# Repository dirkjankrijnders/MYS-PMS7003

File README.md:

# MYS-PMS7003
Mysensors experimental node with switch mode power supply, NRF24, arduino, ESP-03 and PM-7003

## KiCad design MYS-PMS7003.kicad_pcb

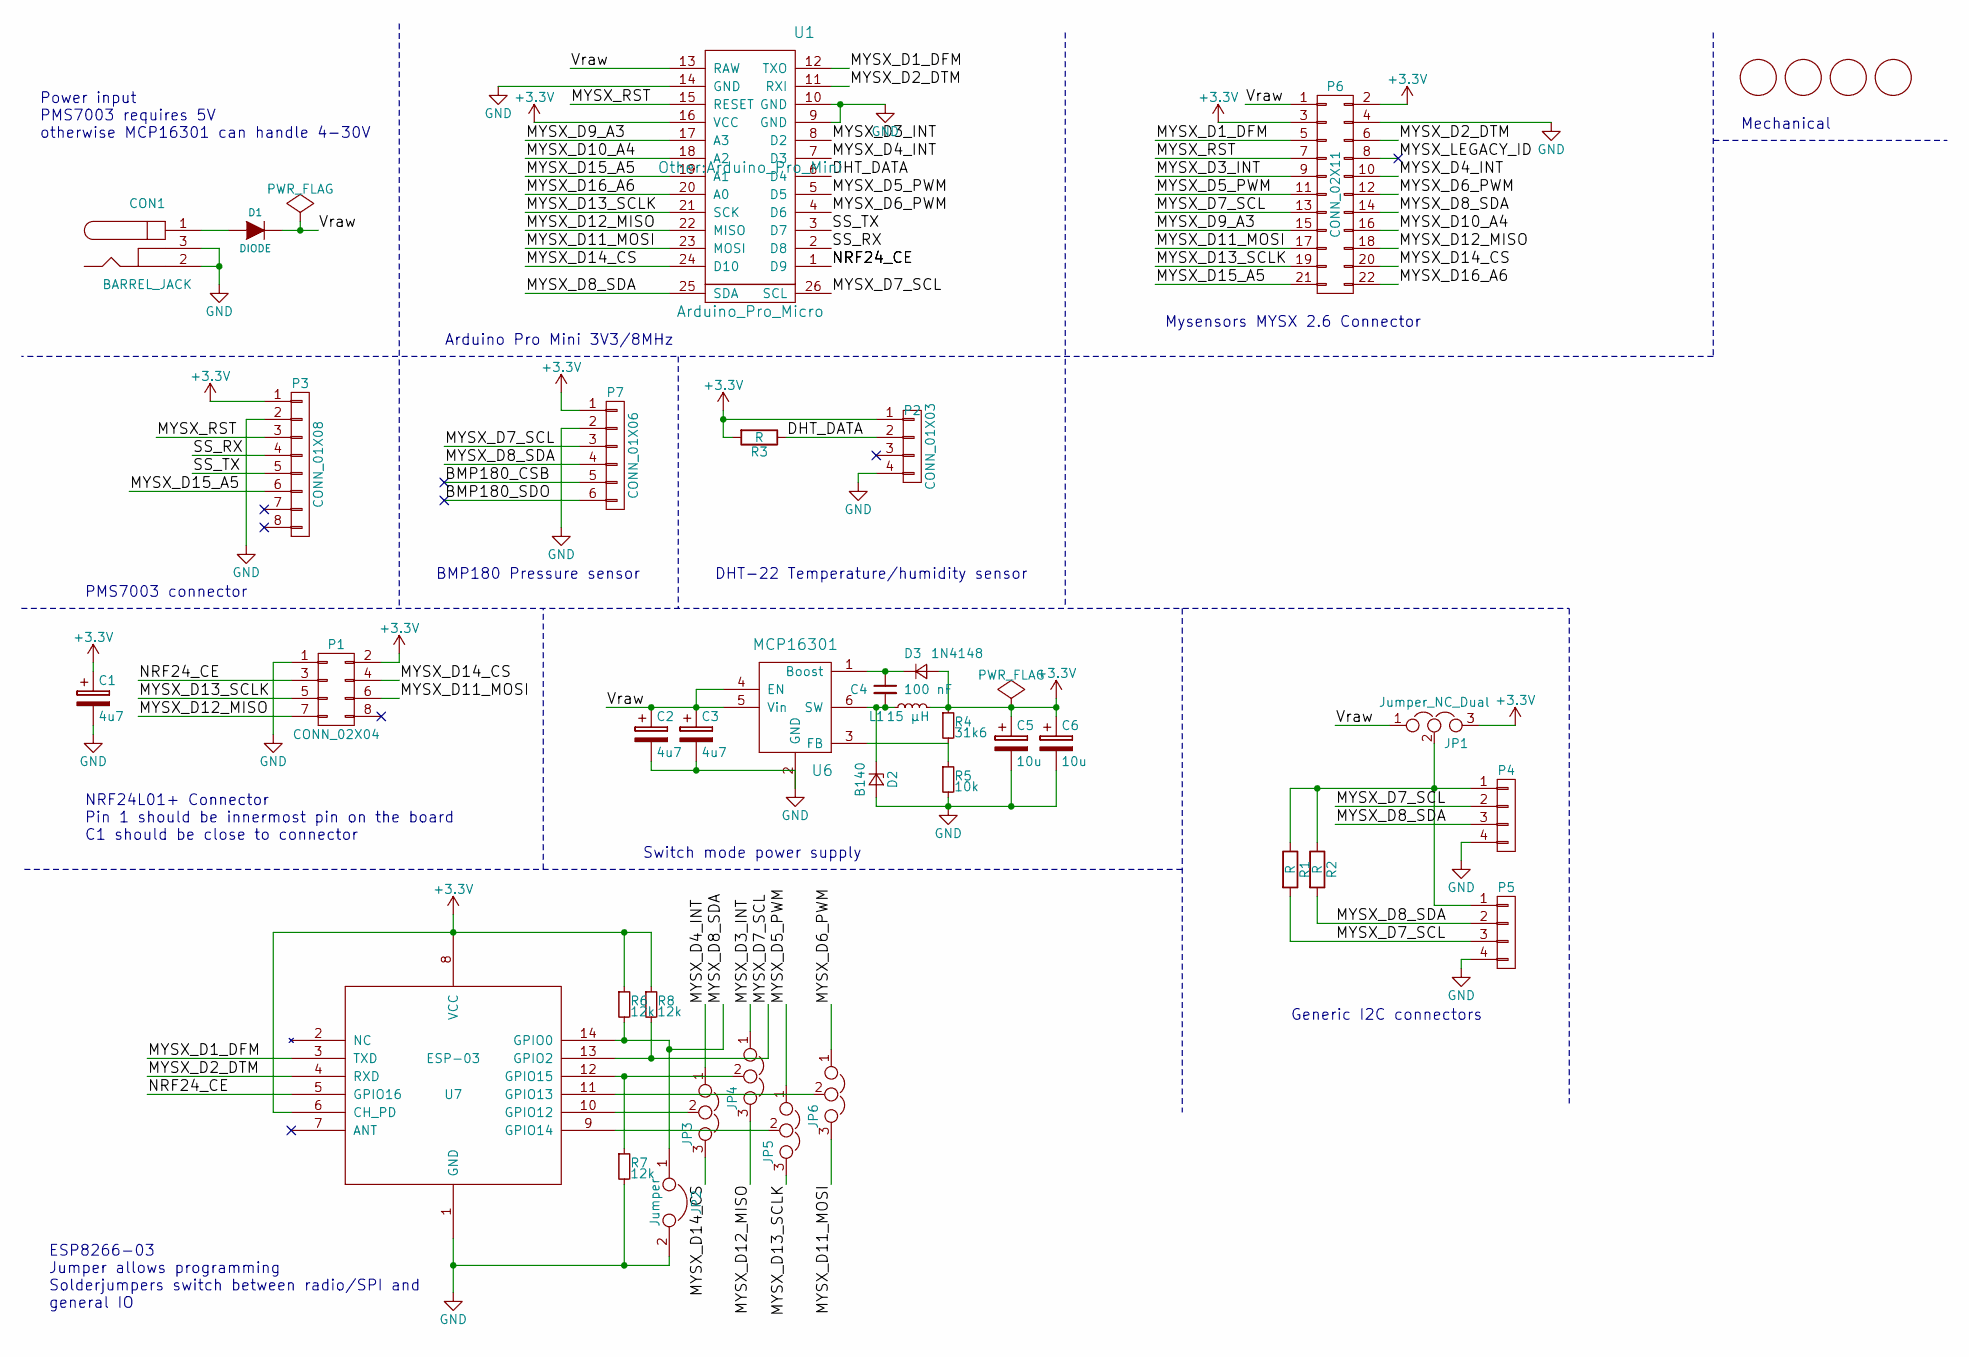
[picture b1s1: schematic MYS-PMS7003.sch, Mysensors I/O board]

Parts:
C1, C2, C3: 4u7; R_1210_HandSoldering
C4: 100 nF; R_0805_HandSoldering
C5, C6: 10u; R_0805_HandSoldering
CON1: BARREL_JACK
D1: DIODE; D_SMA-SMB_Universal_Handsoldering
D2: B140; D_SMA
D3: 1N4148; D_SOD-323_HandSoldering
JP1, JP3, JP4, JP5: Jumper_NC_Dual; Pin_Header_Straight_1x03_Pitch2.54mm
JP2: Jumper; Pin_Header_Angled_1x02_Pitch2.54mm
JP6: Jumper_NC_Dual; SolderJumper2way
L1: 15 μH; L_Coilcraft_MSS6132
P1: CONN_02X04; Pin_Header_Straight_2x04_Pitch2.54mm
P2: CONN_01X03; Pin_Header_Straight_1x04_Pitch2.54mm
P3: CONN_01X08; Pin_Header_Straight_1x08_Pitch1.27mm
P4, P5: CONN_01X04; Pin_Header_Straight_1x04_Pitch2.54mm
P6: CONN_02X11; Pin_Header_Straight_2x11_Pitch2.54mm
P7: CONN_01X06; Pin_Header_Straight_1x06_Pitch2.54mm
R1, R2, R3: R; R_0805_HandSoldering
R4: 31k6; R_0805_HandSoldering
R5: 10k; R_0805_HandSoldering
R6, R7, R8: 12k; R_0805_HandSoldering
U1: Arduino_Pro_Micro; Arduino_Pro_Mini
U2, U3, U4, U5: M3_Mounting_hole; MountingHole_3mm
U6: MCP16301; SOT-23-6_Handsoldering
U7: ESP-03

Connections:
+3V3: C1.1, C5.1, C6.1, D3.2 (A), JP1.3, L1.2, P1.2, P2.1, P3.1, P6.2, P6.3, P7.1, R3.2, R4.1, R6.1, R8.1, U1.16 (VCC), U7.6 (CH_PD), U7.8 (VCC); also elsewhere on the board
/BMP180_CSB: P7.5
/BMP180_SDO: P7.6
/DHT_DATA: P2.2, R3.1, U1.6 (D4)
/MYSX_D1_DFM: P6.5, U1.12 (TXO), U7.3 (TXD); also elsewhere on the board
/MYSX_D2_DTM: P6.6, U1.11 (RXI), U7.4 (RXD); also elsewhere on the board
/MYSX_D3_INT: JP4.1, P6.9, U1.8 (D2)
/MYSX_D4_INT: JP3.1, P6.10, U1.7 (D3)
/MYSX_D5_PWM: JP5.1, P6.11, U1.5 (D5)
/MYSX_D6_PWM: JP6.1, P6.12, U1.4 (D6)
/MYSX_D7_SCL: P4.2, P5.3, P6.13, P7.3, R1.2, R8.2, U1.26 (SCL), U7.13 (GPIO2); also elsewhere on the board
/MYSX_D8_SDA: JP2.1, P4.3, P5.2, P6.14, P7.4, R2.2, R6.2, U1.25 (SDA), U7.14 (GPIO0); also elsewhere on the board
/MYSX_D9_A3: P6.15, U1.17 (A3)
/MYSX_D10_A4: P6.16, U1.18 (A2)
/MYSX_D11_MOSI: JP6.3, P1.6, P6.17, U1.23 (MOSI)
/MYSX_D12_MISO: JP4.3, P1.7, P6.18, U1.22 (MISO)
/MYSX_D13_SCLK: JP5.3, P1.5, P6.19, U1.21 (SCK)
/MYSX_D14_CS: JP3.3, P1.4, P6.20, U1.24 (D10)
/MYSX_D15_A5: P3.6, P6.21, U1.19 (A1)
/MYSX_D16_A6: P6.22, U1.20 (A0)
/MYSX_LEGACY_ID: P6.8
/MYSX_RST: P3.3, P6.7, U1.15 (RESET)
/NRF24_CE: P1.3, U1.1 (D9), U7.5 (GPIO16); also elsewhere on the board
/SS_RX: P3.4, U1.2 (D8)
/SS_TX: P3.5, U1.3 (D7)
/Vraw: C2.1, C3.1, D1.2 (K), JP1.1, P6.1, U1.13 (RAW), U6.4 (EN), U6.5 (Vin)
GND: C1.2, C2.2, C3.2, C5.2, C6.2, CON1.2, CON1.3, D2.2 (A), JP2.2, P1.1, P2.4, P3.2, P4.4, P5.4, P6.4, P7.2, R5.2, R7.2, U1.9 (GND), U1.10 (GND), U1.14 (GND), U6.2 (GND), U7.1 (GND); also elsewhere on the board
unnamed: C4.1, D3.1 (K), U6.1 (Boost)
unnamed: C4.2, D2.1 (K), L1.1, U6.6 (SW)
unnamed 29: CON1.1, D1.1 (A); also elsewhere on the board
unnamed: JP1.2, P4.1, P5.1, R1.1, R2.1
unnamed 31: JP3.2, U7.10 (GPIO12); also elsewhere on the board
unnamed 32: JP4.2, R7.1, U7.12 (GPIO15); also elsewhere on the board
unnamed 33: JP5.2, U7.9 (GPIO14); also elsewhere on the board
unnamed 34: JP6.2, U7.11 (GPIO13); also elsewhere on the board
unnamed: R4.2, R5.1, U6.3 (FB)

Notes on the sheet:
NRF24L01+ Connector Pin 1 should be innermost pin on the board C1 should be close to connector
PMS7003 connector
Power input PMS7003 requires 5V otherwise MCP16301 can handle 4-30V
Mechanical
BMP180 Pressure sensor
DHT-22 Temperature/humidity sensor
Generic I2C connectors
Mysensors MYSX 2.6 Connector
Switch mode power supply
ESP8266-03 Jumper allows programming Solderjumpers switch between radio/SPI and general IO
Arduino Pro Mini 3V3/8MHz

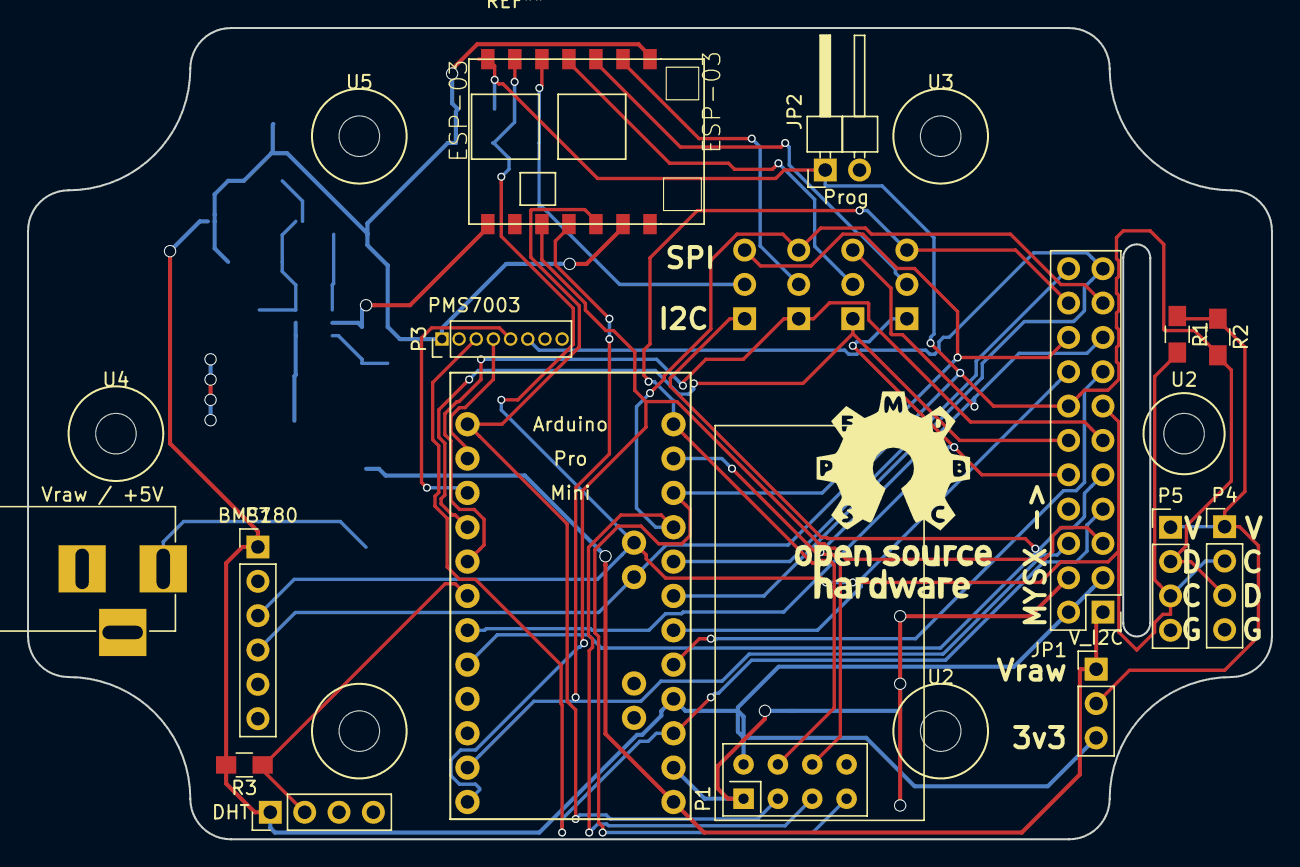
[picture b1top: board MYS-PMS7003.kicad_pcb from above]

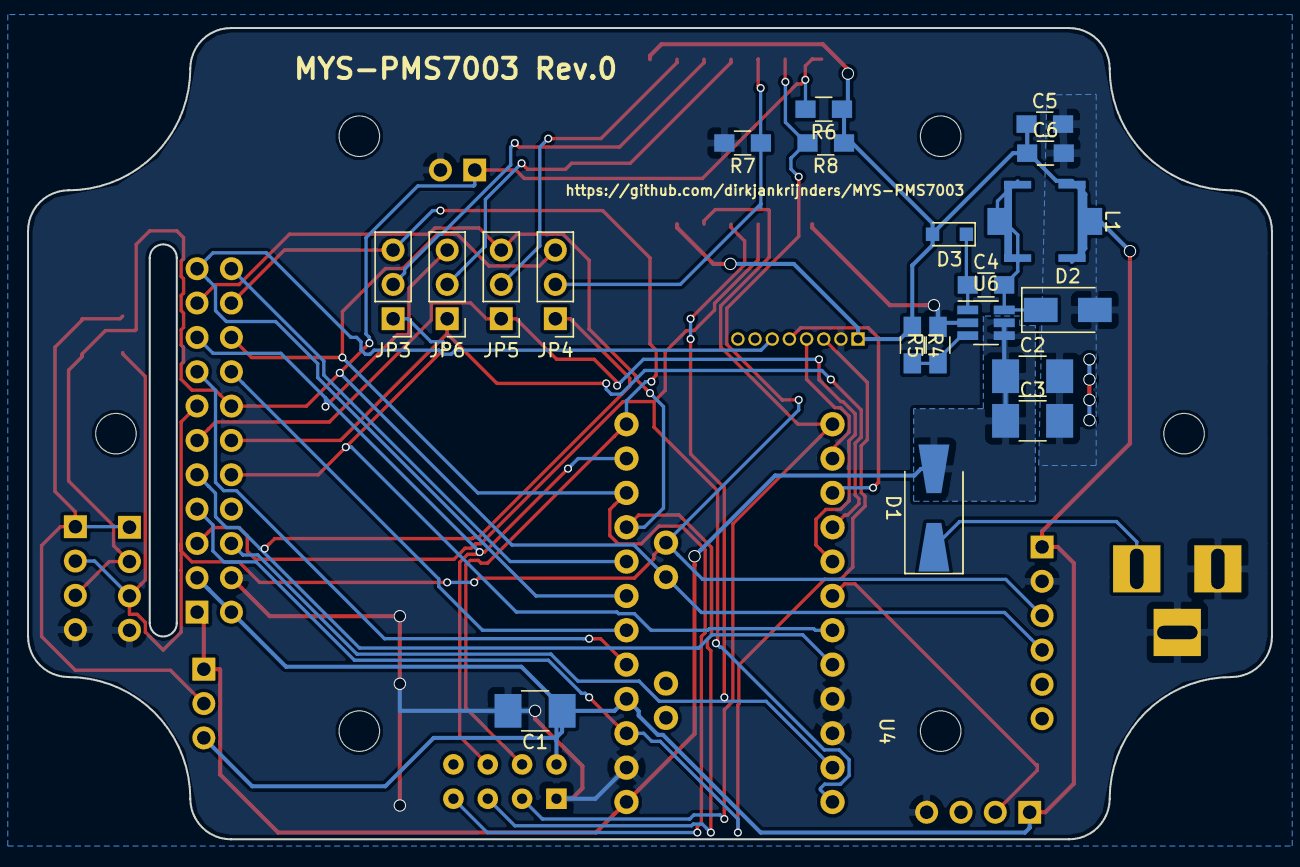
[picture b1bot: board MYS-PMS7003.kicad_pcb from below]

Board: 2 copper layers, 92.0 x 60.0 mm, 41 parts (21 on the bottom side), 33 nets.

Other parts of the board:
ESP-03: ESP-03
U2#2, U4#2: M3_Mounting_hole; MountingHole_3mm
Vraw / +5V: BARREL_JACK

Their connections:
+3V3: ESP-03.6, ESP-03.8; also elsewhere on the board
/MYSX_D1_DFM: ESP-03.3; also elsewhere on the board
/MYSX_D2_DTM: ESP-03.4; also elsewhere on the board
/MYSX_D7_SCL: ESP-03.13; also elsewhere on the board
/MYSX_D8_SDA: ESP-03.14; also elsewhere on the board
/NRF24_CE: ESP-03.5; also elsewhere on the board
GND: ESP-03.1, Vraw / +5V.2, Vraw / +5V.3; also elsewhere on the board
unnamed 29: Vraw / +5V.1; also elsewhere on the board
unnamed 31: ESP-03.10; also elsewhere on the board
unnamed 32: ESP-03.12; also elsewhere on the board
unnamed 33: ESP-03.9; also elsewhere on the board
unnamed 34: ESP-03.11; also elsewhere on the board

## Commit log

2017-06-13 Initial revision of the board
2017-06-13 Added text to silkscreen, added Gerber files, schematic.
2017-06-16 Updated radio module outline, fixed missing tracks
2017-06-16 Created a slot for the MYSX cable to go to the other side of the board
2017-06-16 Switched from the standard footprint to the official MYSX 2.6 footprint
